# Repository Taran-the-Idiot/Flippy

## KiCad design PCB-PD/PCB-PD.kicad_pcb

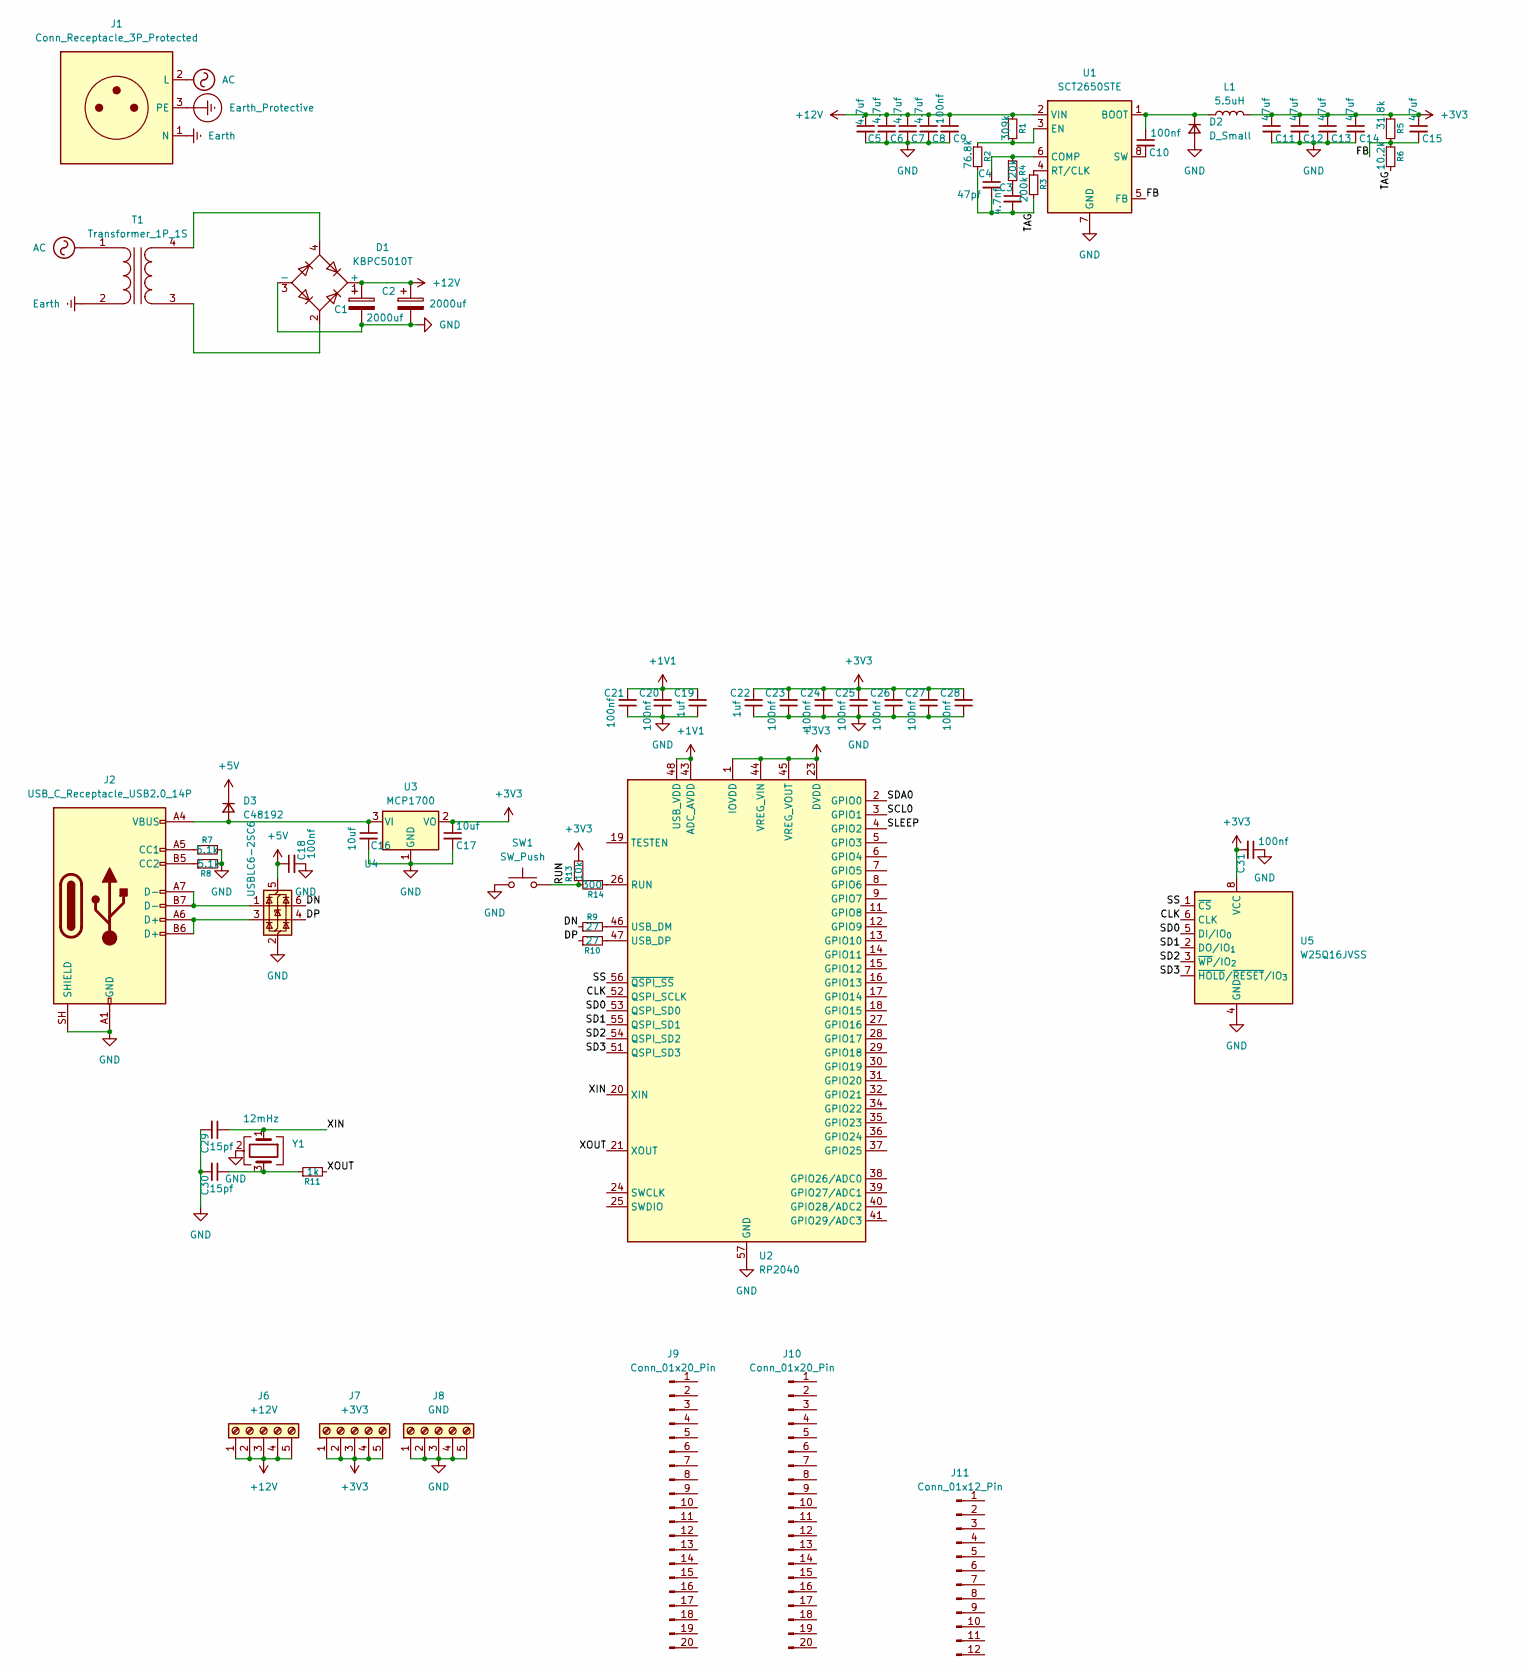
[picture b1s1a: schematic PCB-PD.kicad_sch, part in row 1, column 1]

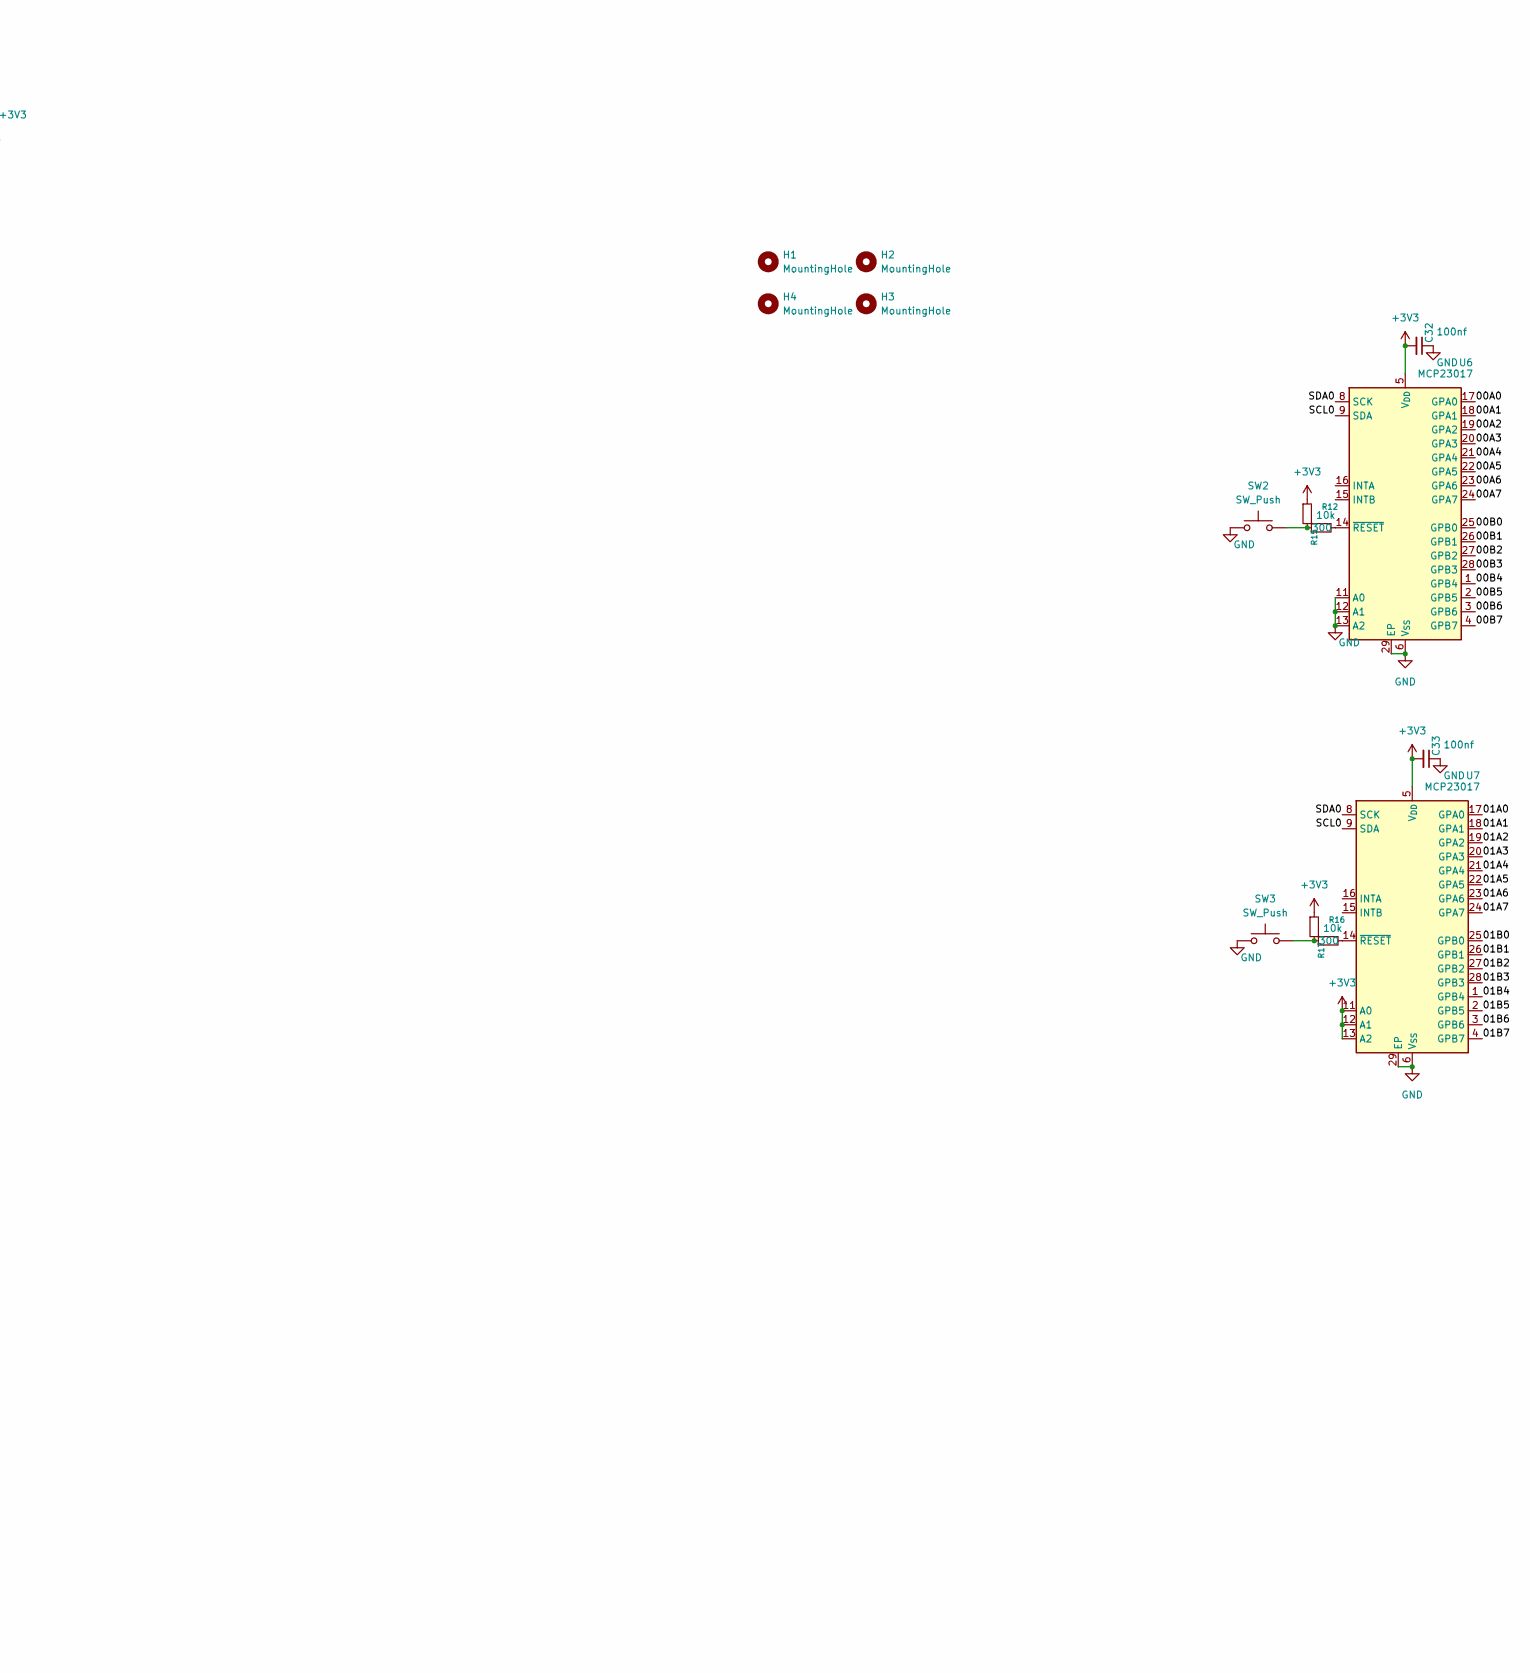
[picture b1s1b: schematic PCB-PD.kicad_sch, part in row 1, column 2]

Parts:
C1, C2: 2000uf
C3: 4.7nf; C_0402_1005Metric_Pad0.74x0.62mm_HandSolder
C4: 47pf; C_0603_1608Metric_Pad1.08x0.95mm_HandSolder
C5, C6, C7, C8: 4.7uf; C_0402_1005Metric_Pad0.74x0.62mm_HandSolder
C9, C10, C18, C20, C21, C23, C24, C25, C26, C27, C28, C31, C32, C33: 100nf; C_0402_1005Metric_Pad0.74x0.62mm_HandSolder
C11, C12, C13, C14, C15: 47uf; C_0603_1608Metric_Pad1.08x0.95mm_HandSolder
C16, C17: 10uf; C_0603_1608Metric_Pad1.08x0.95mm_HandSolder
C19, C22: 1uf; C_0402_1005Metric_Pad0.74x0.62mm_HandSolder
C29, C30: 15pf; C_0603_1608Metric_Pad1.08x0.95mm_HandSolder
D1: KBPC5010T; DIO-BG-TH_KBPC25
D2: D_Small
D3: C48192; USB-C-SMD_20P-P0.50-L6.5-W8.9
H1, H2, H3, H4: MountingHole; MountingHole_3.2mm_M3_Pad_Via
J1: Conn_Receptacle_3P_Protected; 240V Power Outlet
J2: USB_C_Receptacle_USB2.0_14P; USB-C-SMD_20P-P0.50-L6.5-W8.9
J6: +12V; 5P_Screw_Terminal
J7: +3V3; 5P_Screw_Terminal
J8: GND; 5P_Screw_Terminal
J9, J10: Conn_01x20_Pin; PinHeader_1x20_P2.54mm_Vertical
J11: Conn_01x12_Pin; PinHeader_1x12_P2.54mm_Vertical
L1: 5.5uH
R1: 309k; R_0402_1005Metric_Pad0.72x0.64mm_HandSolder
R2: 76.8k; R_0402_1005Metric_Pad0.72x0.64mm_HandSolder
R3: 200k; R_0402_1005Metric_Pad0.72x0.64mm_HandSolder
R4: 20k; R_0402_1005Metric_Pad0.72x0.64mm_HandSolder
R5: 31.8k; R_0402_1005Metric_Pad0.72x0.64mm_HandSolder
R6: 10.2k; R_0402_1005Metric_Pad0.72x0.64mm_HandSolder
R7, R8: 5.1k; R_0402_1005Metric_Pad0.72x0.64mm_HandSolder
R9, R10: 27; R_0402_1005Metric_Pad0.72x0.64mm_HandSolder
R11: 1k; R_0402_1005Metric_Pad0.72x0.64mm_HandSolder
R12, R16: 10k; R_01005_0402Metric
R13: 10k; R_0402_1005Metric_Pad0.72x0.64mm_HandSolder
R14: 300; R_0402_1005Metric_Pad0.72x0.64mm_HandSolder
R15, R17: 300; R_01005_0402Metric
SW1, SW2, SW3: SW_Push; C720477
T1: Transformer_1P_1S
U1: SCT2650STE; SOIC-8-1EP_3.9x4.9mm_P1.27mm_EP2.41x3.3mm
U2: RP2040; QFN-56-1EP_7x7mm_P0.4mm_EP3.2x3.2mm
U3: MCP1700; SOT-23
U4: USBLC6-2SC6; SOT-23-6
U5: W25Q16JVSS; SOIC-8_5.3x5.3mm_P1.27mm
U6, U7: MCP23017; QFN-28-1EP_6x6mm_P0.65mm_EP4.25x4.25mm
Y1: 12mHz; CRYSTAL-SMD_4P-L3.2-W2.5-BL

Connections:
+1V1: C19.2, C20.2, C21.2, U2.43 (ADC_AVDD), U2.48 (USB_VDD)
+3V3: C11.1, C12.1, C13.1, C14.1, C15.1, C17.1, C22.2, C23.2, C24.2, C25.2, C26.2, C27.2, C28.2, C31.2, C32.2, C33.2, J7.1, J7.2, J7.3, J7.4, J7.5, L1.2, R5.1, R12.1, R13.2, R16.1, U2.1 (IOVDD), U2.10 (IOVDD), U2.22 (IOVDD), U2.23 (DVDD), U2.33 (IOVDD), U2.42 (IOVDD), U2.44 (VREG_VIN), U2.45 (VREG_VOUT), U2.49 (IOVDD), U2.50 (DVDD), U3.2 (VO), U5.8 (VCC), U6.5 (V_{DD}), U7.5 (V_{DD}), U7.11 (A0), U7.12 (A1), U7.13 (A2)
+5V: C18.1, D3.1 (K), U4.5 (VBUS)
+12V: C1.1, C2.1, C5.1, C6.1, C7.1, C8.1, C9.1, D1.1 (+), J6.1, J6.2, J6.3, J6.4, J6.5, R1.1, U1.2 (VIN)
/00A0: U6.17 (GPA0)
/00A1: U6.18 (GPA1)
/00A2: U6.19 (GPA2)
/00A3: U6.20 (GPA3)
/00A4: U6.21 (GPA4)
/00A5: U6.22 (GPA5)
/00A6: U6.23 (GPA6)
/00A7: U6.24 (GPA7)
/00B0: U6.25 (GPB0)
/00B1: U6.26 (GPB1)
/00B2: U6.27 (GPB2)
/00B3: U6.28 (GPB3)
/00B4: U6.1 (GPB4)
/00B5: U6.2 (GPB5)
/00B6: U6.3 (GPB6)
/00B7: U6.4 (GPB7)
/01A0: U7.17 (GPA0)
/01A1: U7.18 (GPA1)
/01A2: U7.19 (GPA2)
/01A3: U7.20 (GPA3)
/01A4: U7.21 (GPA4)
/01A5: U7.22 (GPA5)
/01A6: U7.23 (GPA6)
/01A7: U7.24 (GPA7)
/01B0: U7.25 (GPB0)
/01B1: U7.26 (GPB1)
/01B2: U7.27 (GPB2)
/01B3: U7.28 (GPB3)
/01B4: U7.1 (GPB4)
/01B5: U7.2 (GPB5)
/01B6: U7.3 (GPB6)
/01B7: U7.4 (GPB7)
/CLK: U2.52 (QSPI_SCLK), U5.6 (CLK)
/DN: R9.1, U4.6 (I/O1)
/DP: R10.1, U4.4 (I/O2)
/FB: C15.2, R5.2, R6.1, U1.5 (FB)
/RUN: R13.1, R14.2, SW1.2
/SCL0: U2.3 (GPIO1), U6.9 (SDA), U7.9 (SDA)
/SD0: U2.53 (QSPI_SD0), U5.5 (DI/IO_{0})
/SD1: U2.55 (QSPI_SD1), U5.2 (DO/IO_{1})
/SD2: U2.54 (QSPI_SD2), U5.3 (~WP/IO_{2})
/SD3: U2.51 (QSPI_SD3), U5.7 (~HOLD/~RESET/IO_{3})
/SDA0: U2.2 (GPIO0), U6.8 (SCK), U7.8 (SCK)
/SLEEP: U2.4 (GPIO2)
/SS: U2.56 (~QSPI_SS), U5.1 (~CS)
/TAG: C3.2, C4.2, R2.2, R3.2, R6.2
/XIN: C29.1, U2.20 (XIN), Y1.1
/XOUT: R11.2, U2.21 (XOUT)
AC: J1.2 (L), T1.1 (AA)
Earth: J1.1 (N), T1.2 (AB)
Earth_Protective: J1.3 (PE)
GND: C1.2, C2.2, C5.2, C6.2, C7.2, C8.2, C9.2, C11.2, C12.2, C13.2, C14.2, C16.2, C17.2, C18.2, C19.1, C20.1, C21.1, C22.1, C23.1, C24.1, C25.1, C26.1, C27.1, C28.1, C29.2, C30.2, C31.1, C32.1, C33.1, D1.3 (-), D2.2 (A), J2.A1 (GND), J2.A12 (GND), J2.B1 (GND), J2.B12 (GND), J2.SH (SHIELD), J8.1, J8.2, J8.3, J8.4, J8.5, R7.2, R8.2, SW1.1, SW2.1, SW3.1, U1.7 (GND), U1.9 (GND), U2.57 (GND), U3.1 (GND), U4.2 (GND), U5.4 (GND), U6.6 (V_{SS}), U6.11 (A0), U6.12 (A1), U6.13 (A2), U6.29 (EP), U7.6 (V_{SS}), U7.29 (EP), Y1.2 (G), Y1.4 (G)
unnamed: C3.1, R4.2
unnamed: C30.1, R11.1, Y1.3
unnamed: C10.1, D2.1 (K), L1.1, U1.1 (BOOT)
unnamed: C16.1, D3.2 (A), J2.A4 (VBUS), J2.A9 (VBUS), J2.B4 (VBUS), J2.B9 (VBUS), U3.3 (VI)
unnamed: J2.A5 (CC1), R7.1
unnamed: J2.B5 (CC2), R8.1
unnamed: J2.A6 (D+), J2.B6 (D+), U4.3 (I/O2)
unnamed: J2.A7 (D-), J2.B7 (D-), U4.1 (I/O1)
unnamed: R12.2, R15.1, SW2.2
unnamed: R16.2, R17.1, SW3.2
unnamed: D1.2, T1.3 (SA)
unnamed: D1.4, T1.4 (SB)
unnamed: C4.1, R4.1, U1.6 (COMP)
unnamed: R1.2, R2.1, U1.3 (EN)
unnamed: R3.1, U1.4 (RT/CLK)
unnamed: C10.2, U1.8 (SW)
unnamed: R14.1, U2.26 (RUN)
unnamed: R9.2, U2.46 (USB_DM)
unnamed: R10.2, U2.47 (USB_DP)
unnamed: R15.2, U6.14 (~RESET)
unnamed: R17.2, U7.14 (~RESET)

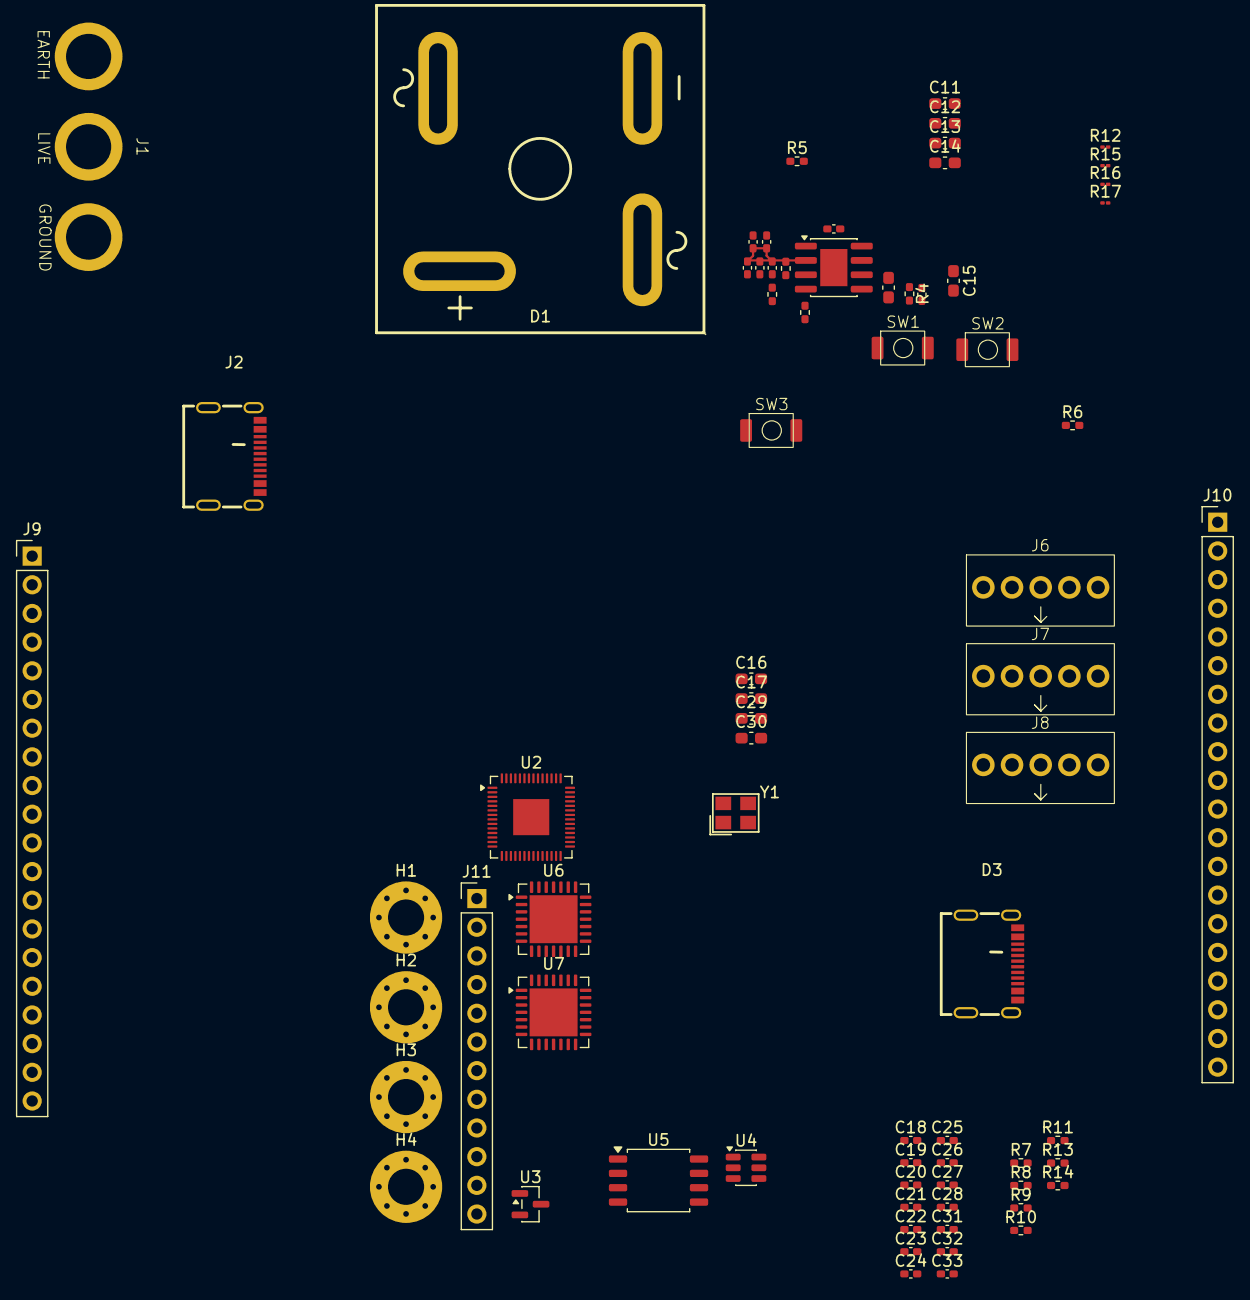
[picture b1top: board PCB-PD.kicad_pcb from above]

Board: 2 copper layers, 73 parts (0 on the bottom side), 39 nets.

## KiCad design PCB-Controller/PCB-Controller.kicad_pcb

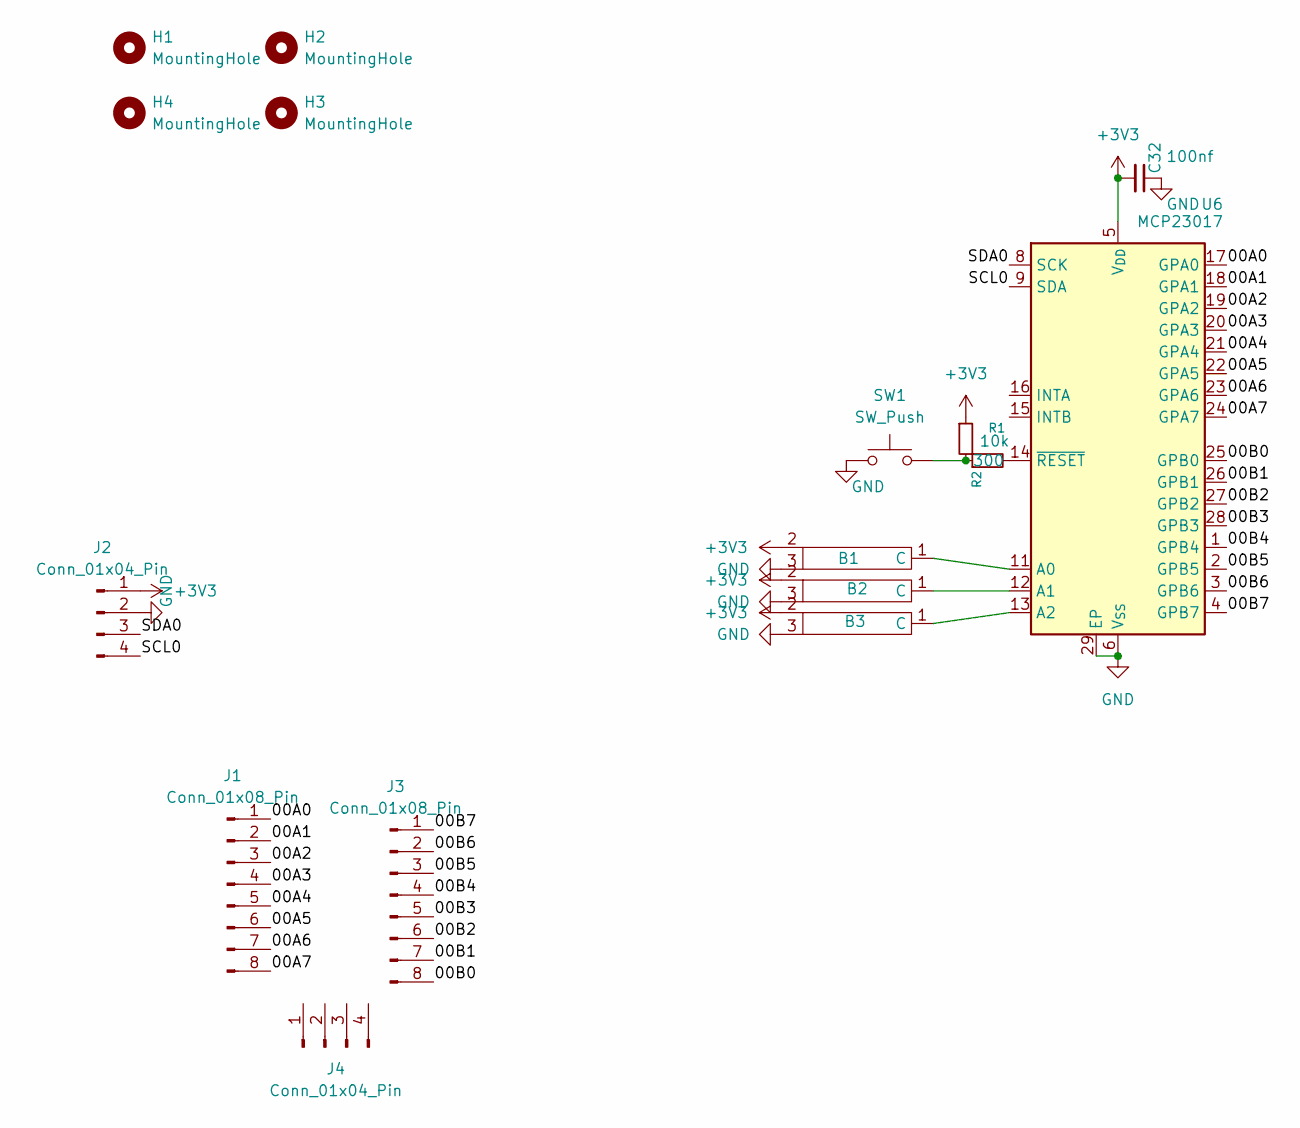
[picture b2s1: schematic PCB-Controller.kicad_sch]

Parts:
B1, B2, B3: 3P_Bridge
C32: 100nf; C_0402_1005Metric_Pad0.74x0.62mm_HandSolder
H1, H2, H3, H4: MountingHole; MountingHole_3.2mm_M3_Pad_Via
J1, J3: Conn_01x08_Pin; PinHeader_1x08_P2.54mm_Vertical
J2, J4: Conn_01x04_Pin; PinHeader_1x04_P2.54mm_Vertical
R1: 10k; R_01005_0402Metric
R2: 300; R_01005_0402Metric
SW1: SW_Push; C720477
U6: MCP23017; QFN-28-1EP_6x6mm_P0.65mm_EP4.25x4.25mm

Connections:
+3V3: B1.2, B2.2, B3.2, C32.2, J2.1, R1.1, U6.5 (V_{DD})
/00A0: J1.1, U6.17 (GPA0)
/00A1: J1.2, U6.18 (GPA1)
/00A2: J1.3, U6.19 (GPA2)
/00A3: J1.4, U6.20 (GPA3)
/00A4: J1.5, U6.21 (GPA4)
/00A5: J1.6, U6.22 (GPA5)
/00A6: J1.7, U6.23 (GPA6)
/00A7: J1.8, U6.24 (GPA7)
/00B0: J3.8, U6.25 (GPB0)
/00B1: J3.7, U6.26 (GPB1)
/00B2: J3.6, U6.27 (GPB2)
/00B3: J3.5, U6.28 (GPB3)
/00B4: J3.4, U6.1 (GPB4)
/00B5: J3.3, U6.2 (GPB5)
/00B6: J3.2, U6.3 (GPB6)
/00B7: J3.1, U6.4 (GPB7)
/SCL0: J2.4, U6.9 (SDA)
/SDA0: J2.3, U6.8 (SCK)
GND: B1.3, B2.3, B3.3, C32.1, J2.2, SW1.1, U6.6 (V_{SS}), U6.29 (EP)
unnamed: B1.1 (C_1), U6.11 (A0)
unnamed: B2.1 (C_1), U6.12 (A1)
unnamed: B3.1 (C_1), U6.13 (A2)
unnamed: R1.2, R2.1, SW1.2
unnamed: R2.2, U6.14 (~RESET)

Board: 2 copper layers, 15 parts (0 on the bottom side), 25 nets, no tracks yet.

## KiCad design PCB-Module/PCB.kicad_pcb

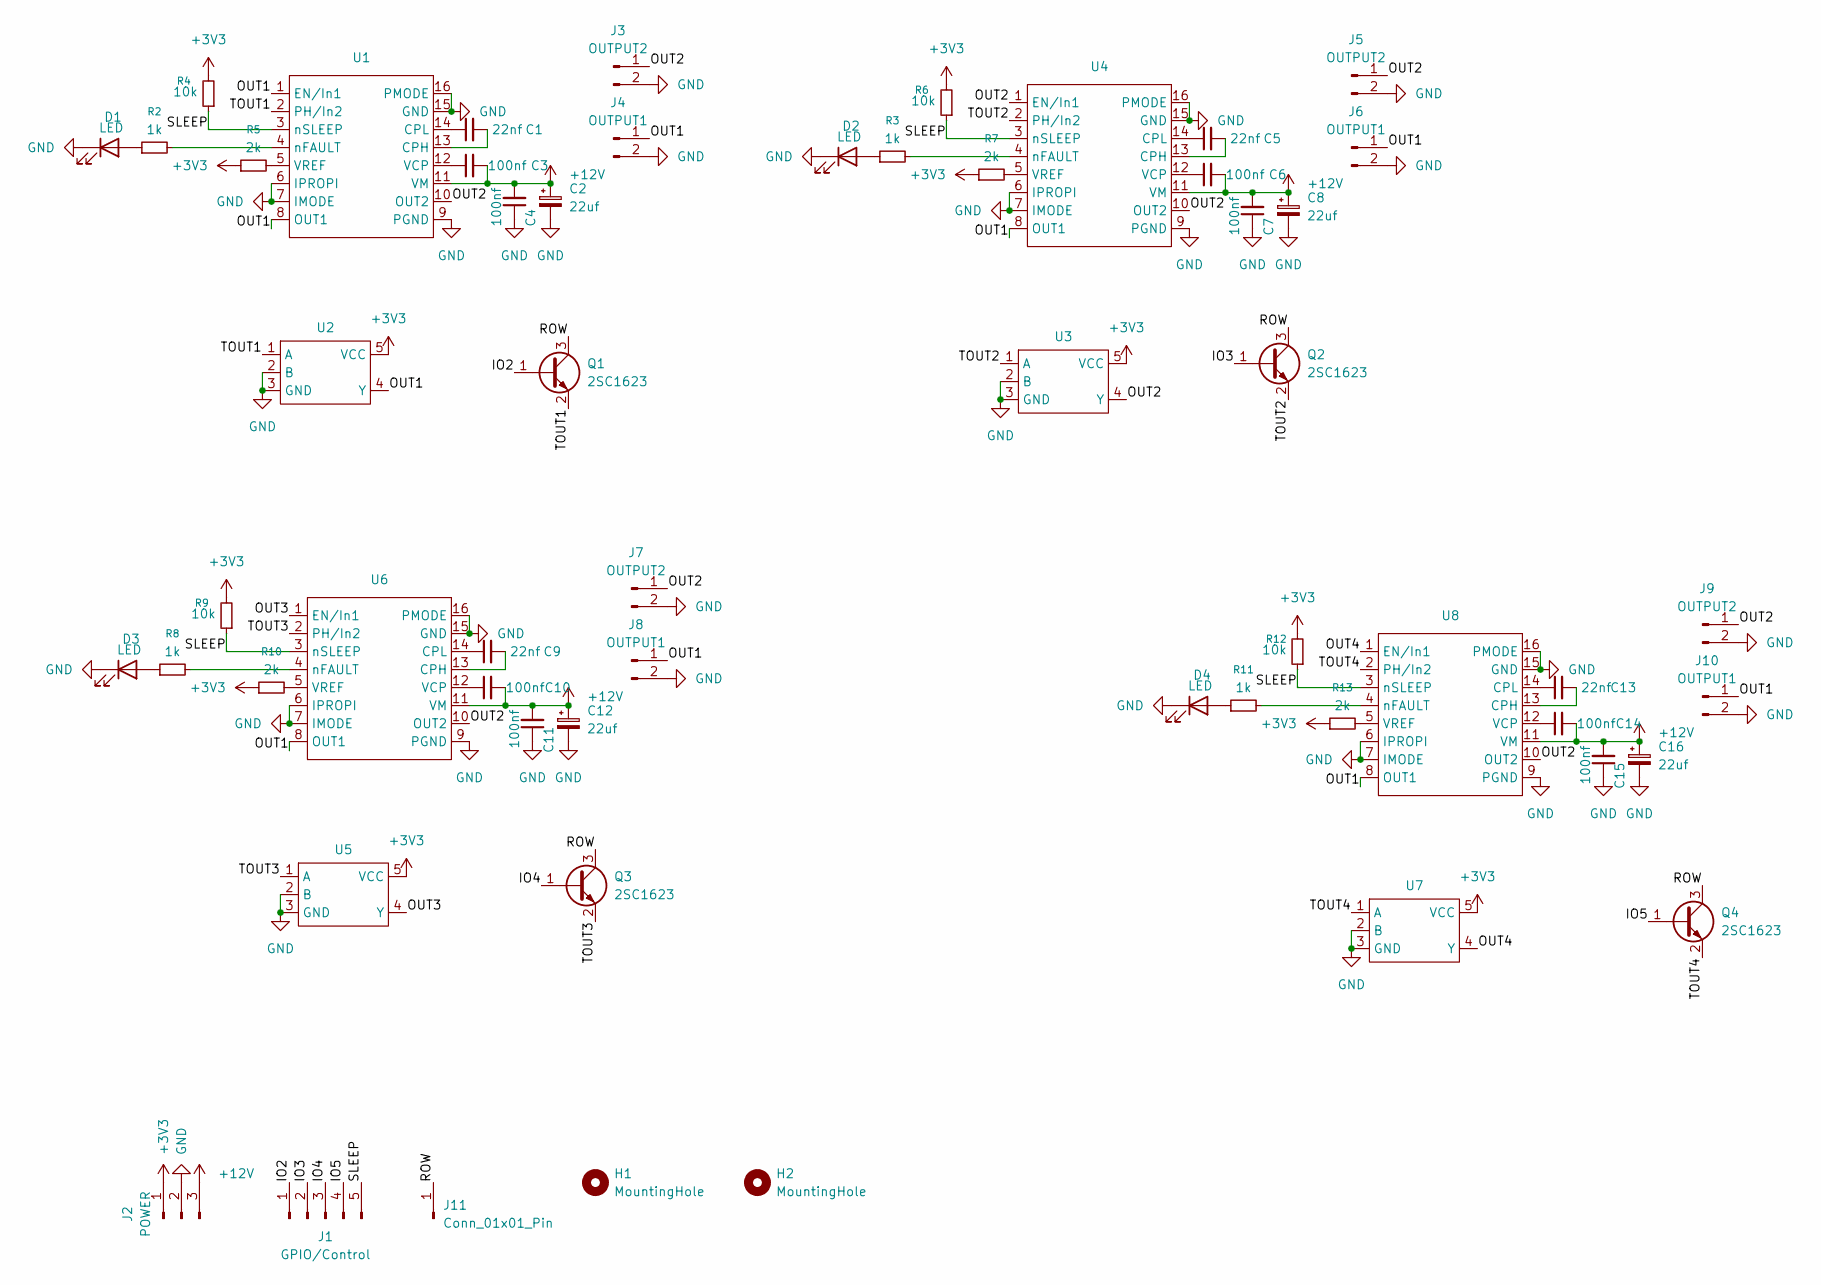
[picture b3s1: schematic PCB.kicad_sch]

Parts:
C1, C5, C9, C13: 22nf; C_0402_1005Metric
C2, C8, C12, C16: 22uf; CP_Radial_D5.0mm_P2.00mm
C3, C4, C6, C7, C10, C11, C14, C15: 100nf; C_0402_1005Metric
D1, D2, D3, D4: LED; LED_0805_2012Metric
H1, H2: MountingHole; MountingHole_2.2mm_M2_Pad_TopOnly
J1: GPIO/Control; PinHeader_1x05_P2.54mm_Vertical
J2: POWER; 3P_Screw_Terminal
J3, J5, J7, J9: OUTPUT2; Electromagnet Power Output
J4, J6, J8, J10: OUTPUT1; Electromagnet Power Output
J11: Conn_01x01_Pin; PinHeader_1x01_P2.54mm_Vertical
Q1, Q2, Q3, Q4: 2SC1623; SOT-23
R2, R3, R8, R11: 1k; C_0402_1005Metric
R4, R6, R9, R12: 10k; C_0402_1005Metric
R5, R7, R10, R13: 2k; C_0402_1005Metric
U1, U4, U6, U8: HTSSOP-16-1EP_4.4x5mm_P0.65mm_EP3.4x5mm_Mask2.46x2.31mm_The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
U2, U3, U5, U7: SOT-353_SC-70-5

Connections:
+3V3: J2.1, R4.2, R5.1, R6.2, R7.1, R9.2, R10.1, R12.2, R13.1, U2.5 (VCC), U3.5 (VCC), U5.5 (VCC), U7.5 (VCC)
+12V: C2.1, C3.2, C4.2, C6.2, C7.2, C8.1, C10.2, C11.2, C12.1, C14.2, C15.2, C16.1, J2.3, U1.11 (VM), U4.11 (VM), U6.11 (VM), U8.11 (VM)
/IO2: J1.1, Q1.1 (B)
/IO3: J1.2, Q2.1 (B)
/IO4: J1.3, Q3.1 (B)
/IO5: J1.4, Q4.1 (B)
/OUT1: J4.1, J6.1, J8.1, J10.1, U1.1 (EN/In1), U1.8 (OUT1), U2.4 (Y), U4.8 (OUT1), U6.8 (OUT1), U8.8 (OUT1)
/OUT2: J3.1, J5.1, J7.1, J9.1, U1.10 (OUT2), U3.4 (Y), U4.1 (EN/In1), U4.10 (OUT2), U6.10 (OUT2), U8.10 (OUT2)
/OUT3: U5.4 (Y), U6.1 (EN/In1)
/OUT4: U7.4 (Y), U8.1 (EN/In1)
/ROW: J11.1 (Pin_1_1), Q1.3 (C), Q2.3 (C), Q3.3 (C), Q4.3 (C)
/SLEEP: J1.5, R4.1, R6.1, R9.1, R12.1, U1.3 (nSLEEP), U4.3 (nSLEEP), U6.3 (nSLEEP), U8.3 (nSLEEP)
/TOUT1: Q1.2 (E), U1.2 (PH/In2), U2.1 (A)
/TOUT2: Q2.2 (E), U3.1 (A), U4.2 (PH/In2)
/TOUT3: Q3.2 (E), U5.1 (A), U6.2 (PH/In2)
/TOUT4: Q4.2 (E), U7.1 (A), U8.2 (PH/In2)
GND: C2.2, C4.1, C7.1, C8.2, C11.1, C12.2, C15.1, C16.2, D1.1 (K), D2.1 (K), D3.1 (K), D4.1 (K), J2.2, J3.2, J4.2, J5.2, J6.2, J7.2, J8.2, J9.2, J10.2, U1.6 (IPROPI), U1.7 (IMODE), U1.9 (PGND), U1.15 (GND), U1.16 (PMODE), U2.2 (B), U2.3 (GND), U3.2 (B), U3.3 (GND), U4.6 (IPROPI), U4.7 (IMODE), U4.9 (PGND), U4.15 (GND), U4.16 (PMODE), U5.2 (B), U5.3 (GND), U6.6 (IPROPI), U6.7 (IMODE), U6.9 (PGND), U6.15 (GND), U6.16 (PMODE), U7.2 (B), U7.3 (GND), U8.6 (IPROPI), U8.7 (IMODE), U8.9 (PGND), U8.15 (GND), U8.16 (PMODE)
unnamed: D1.2 (A), R2.1
unnamed: D2.2 (A), R3.1
unnamed: D3.2 (A), R8.1
unnamed: D4.2 (A), R11.1
unnamed: C1.2, U1.13 (CPH)
unnamed: C1.1, U1.14 (CPL)
unnamed: C3.1, U1.12 (VCP)
unnamed: R5.2, U1.5 (VREF)
unnamed: R2.2, U1.4 (nFAULT)
unnamed: C5.2, U4.13 (CPH)
unnamed: C5.1, U4.14 (CPL)
unnamed: C6.1, U4.12 (VCP)
unnamed: R7.2, U4.5 (VREF)
unnamed: R3.2, U4.4 (nFAULT)
unnamed: C9.2, U6.13 (CPH)
unnamed: C9.1, U6.14 (CPL)
unnamed: C10.1, U6.12 (VCP)
unnamed: R10.2, U6.5 (VREF)
unnamed: R8.2, U6.4 (nFAULT)
unnamed: C13.2, U8.13 (CPH)
unnamed: C13.1, U8.14 (CPL)
unnamed: C14.1, U8.12 (VCP)
unnamed: R13.2, U8.5 (VREF)
unnamed: R11.2, U8.4 (nFAULT)

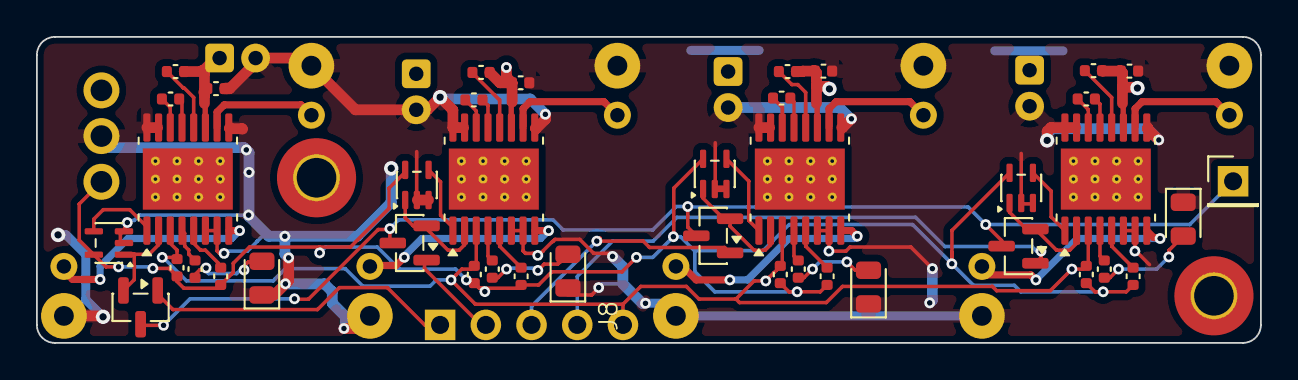
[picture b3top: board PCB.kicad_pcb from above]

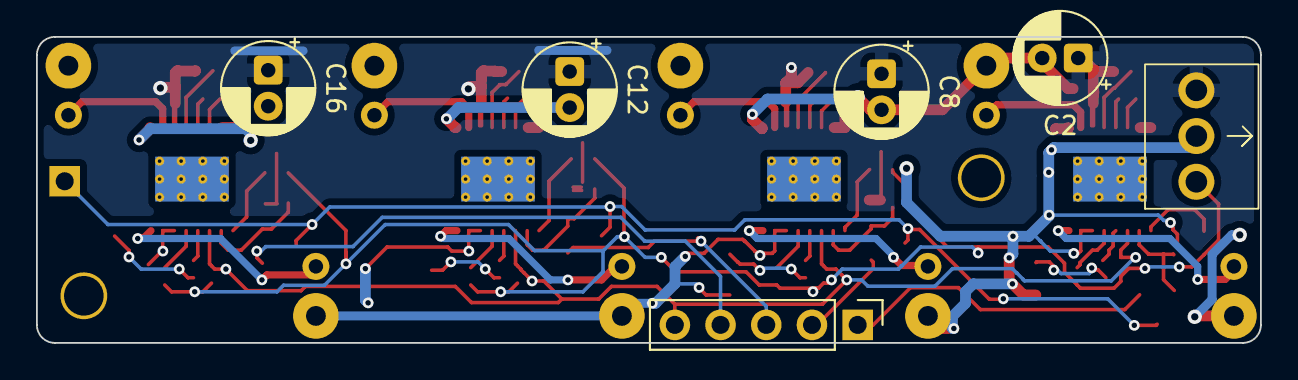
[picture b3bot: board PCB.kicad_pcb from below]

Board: 2 copper layers, 68.0 x 17.0 mm, 57 parts (6 on the bottom side), 41 nets.

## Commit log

2026-06-17 kill me
2026-06-17 slime dookie
2026-06-18 commite
2026-06-21 bleh
2026-06-22 bleh2
2026-06-22 potato
2026-06-23 end me
